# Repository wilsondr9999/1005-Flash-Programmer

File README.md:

# Flash Programmer
Copyright © 2021 by Dan WIlson

This is a simple PCB, firmware, and software that can read and write binary image files to the Microchip SST39 series of flash ROMs.  These flash ROMs are one of the very few flash ROMs on the market that are still active production and in DIP packages, making them a popular replacement for the difficult-to-find AT28 series of EEPROMs.

This programmer handles the SST39SF010, SST39SF020, and SST39SF040 parts (128KB, 256KB, and 512KB respectively).

This programmer’s PCB design uses all through-hole parts for easy soldering.  The general design is based on Ben Eater’s [Arduino-based Flash Programmer](https://www.youtube.com/watch?v=K88pgWhEb1M), using a microcontroller and shift registers to increase the number of available outputs.  Ben’s microcontroller is the Arduino Nano, here I’m using a Microchip PIC16.

The firmware on the PIC16 implements a command protocol that runs over a serial interface.  The board contains a simple RS232 serial level shifter that allows the PC to communicate with the microcontroller.

On the PC, a command line program is provided to read and write to the flash memory.  The command line program is written in Visual C# with Visual Studio.

You can order the PCBs directly from Oshpark with [this](https://oshpark.com/import?url=https://github.com/wilsondr9999/1005-Flash-Programmer/raw/main/1005-Flash-Programmer.zip) link.

Several different licenses apply to this repository and the files within.

All schematics and circuit board designs in the project (all KiCAD files) are licensed under the CERN Open Hardware License Version 2 - Strongly Reciprocal (CERN-OHL-S).

All software and firmware code in the project (all MPLAB and Visual Studio files) are licensed under the GNU Affero General Public License v3.0 (AGPL 3.0).

Bill of Materials, pictures, and documentation (i.e. all other files not covered by the other two licenses above) are licensed under the Creative Commons Attribution Share Alike 4.0 International License (CC-BY-SA-4.0).

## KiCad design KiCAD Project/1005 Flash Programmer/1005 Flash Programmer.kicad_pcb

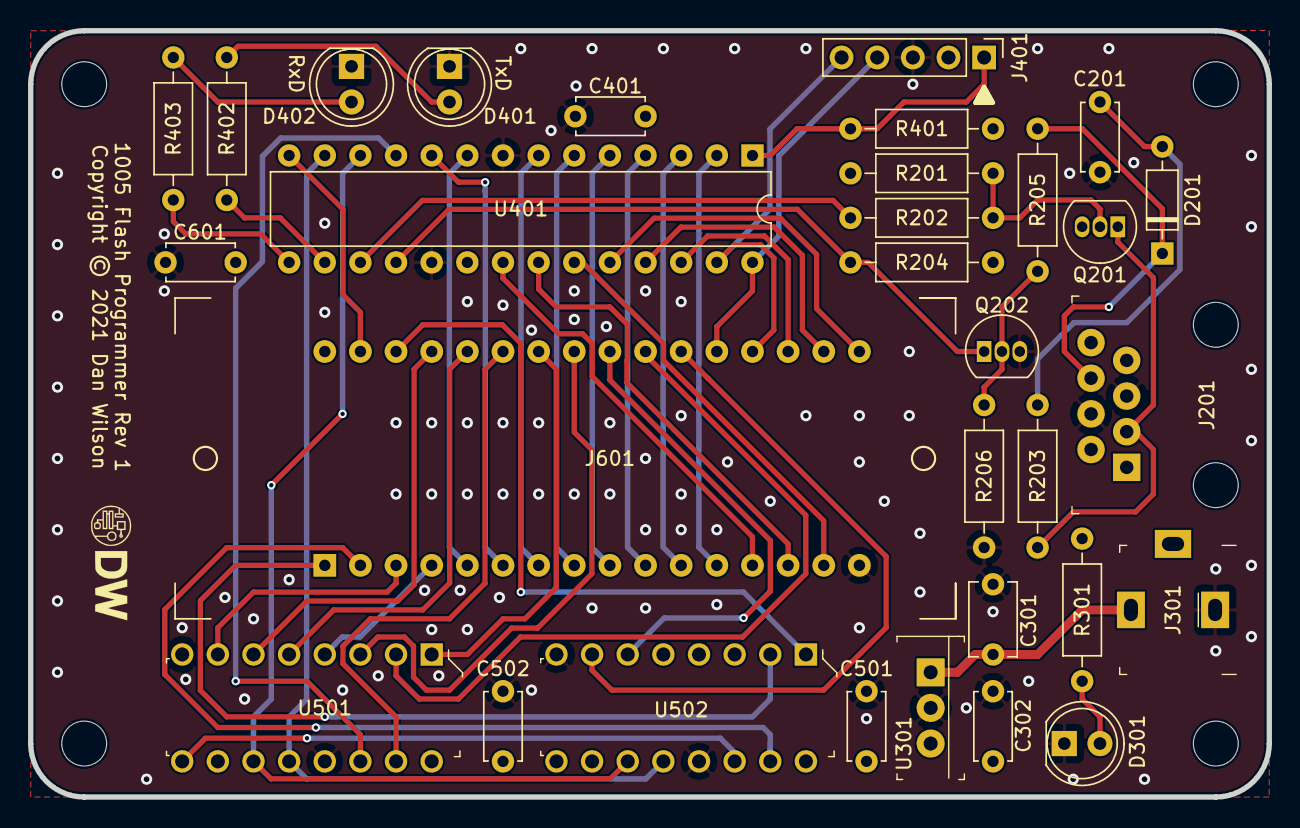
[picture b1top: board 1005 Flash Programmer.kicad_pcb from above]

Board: 4 copper layers, 88.3 x 54.6 mm, 35 parts (0 on the bottom side), 50 nets.

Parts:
C201, C302, C401, C501, C502, C601: 0.1uF; C_Disc_D4.7mm_W2.5mm_P5.00mm
C301: 0.33uF; C_Disc_D5.1mm_W3.2mm_P5.00mm
D201: 1N4148; D_DO-35_SOD27_P7.62mm_Horizontal
D301, D401, D402: LED; LED_D5.0mm
H101, H102, H103, H104: MountingHole; MountingHole_3.2mm_M3
J201: A-2004-2-4-LP-N-R; Ethernet_Jack_54602-908LF
J301: Barrel_Jack_Switch; Barrel_Jack_5.5mmODx2.1mmID_PJ-102A
J401: ICSP; PinHeader_1x05_P2.54mm_Vertical
J601: 32-6554-10
Q201: BC558; TO-92_Inline
Q202: BC548; TO-92_Inline
R201, R202, R204, R401: 10K; R_Axial_DIN0207_L6.3mm_D2.5mm_P10.16mm_Horizontal
R203, R205, R206: 4.7K; R_Axial_DIN0207_L6.3mm_D2.5mm_P10.16mm_Horizontal
R301, R402, R403: 300; R_Axial_DIN0207_L6.3mm_D2.5mm_P10.16mm_Horizontal
U301: L7805CV; TO-220-3
U401: PIC16F15256-xSP; DIP-28_W7.62mm
U501, U502: SN74HC595NE4; DIP-16_W7.62mm

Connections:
/Flash Memory/A0: J601.12, U401.2
/Flash Memory/A1: J601.11, U401.3
/Flash Memory/A2: J601.10, U401.4
/Flash Memory/A3: J601.9, U401.5
/Flash Memory/A4: J601.8, U401.6
/Flash Memory/A5: J601.7, U401.7
/Flash Memory/A6: J601.6, U401.10
/Flash Memory/A7: J601.5, U401.9
/Flash Memory/A8: J601.27, U501.15
/Flash Memory/A9: J601.26, U501.1
/Flash Memory/A10: J601.23, U501.2
/Flash Memory/A11: J601.25, U501.3
/Flash Memory/A12: J601.4, U501.4
/Flash Memory/A13: J601.28, U501.5
/Flash Memory/A14: J601.29, U501.6
/Flash Memory/A15: J601.3, U501.7
/Flash Memory/A16: J601.2, U502.15
/Flash Memory/A17: J601.30, U502.1
/Flash Memory/A18: J601.1, U502.2
/Flash Memory/D0: J601.13, U401.21
/Flash Memory/D1: J601.14, U401.22
/Flash Memory/D2: J601.15, U401.23
/Flash Memory/D3: J601.17, U401.24
/Flash Memory/D4: J601.18, U401.25
/Flash Memory/D5: J601.19, U401.26
/Flash Memory/D6: J401.5, J601.20, U401.27
/Flash Memory/D7: J401.4, J601.21, U401.28
/Flash Memory/~CE: J601.22, U502.7
/Flash Memory/~FL_WE: J601.31, U401.14
/Flash Memory/~OE: J601.24, U502.6
/Micro Controller/LED_uRX: R402.1, U401.16
/Micro Controller/LED_uTX: R403.1, U401.15
/Micro Controller/SR_RCLK: U401.13, U501.12, U502.12
/Micro Controller/SR_SCLK: U401.12, U501.11, U502.11
/Micro Controller/SR_SDATA: U401.11, U501.14
/Micro Controller/USART_uRX: Q202.1, R204.2, U401.18
/Micro Controller/USART_uTX: R202.2, U401.17
/Micro Controller/~MCLR: J401.1, R401.2, U401.1
/UART Level Converter/RxD: J201.3, Q201.1, R203.1
/UART Level Converter/TxD: D201.1, J201.6, R205.1
unnamed: C201.1, D201.2, R203.2
unnamed: C301.1, J301.1, U301.1
unnamed: D301.2, R301.2
unnamed: D401.2, R402.2
unnamed: D402.2, R403.2
unnamed: Q201.2, R201.2, R202.1
unnamed: Q202.2, R205.2, R206.1
unnamed: U501.9, U502.14
VDD: C302.1, C401.1, C501.1, C502.1, C601.1, J401.2, J601.32, Q201.3, R201.1, R204.1, R301.1, R401.1, U301.3, U401.20, U501.10, U501.16, U502.10, U502.16
VSS: C201.2, C301.2, C302.2, C401.2, C501.2, C502.2, C601.2, D301.1, D401.1, D402.1, J201.4, J201.5, J301.2, J401.3, J601.16, Q202.3, R206.2, U301.2, U401.8, U401.19, U501.8, U501.13, U502.8, U502.13

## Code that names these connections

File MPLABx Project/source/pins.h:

/* 
 * File:                pins.h
 * Author:              Dan Wilson
 * Comments:
 * Revision history:    
 */

#ifndef XC_HEADER_PINS_H
#define	XC_HEADER_PINS_H

#include <xc.h> // include processor files - each processor file is guarded.  

// These definitions are to attach convenient names to pins
/*
 * Inputs:  PORTC[7]    UART receive (DTE -> DCE, i.e. computer to PIC)
 * Outputs: PORTC[6]    UART transmit (DCE -> DTE, i.e. PIC to computer)
 *          PORTC[5]    LED for receive
 *          PORTC[4]    LED for transmit
 *          PORTC[0]    Serial data to go out to shift registers
 *          PORTC[1]    Serial clock for shift registers
 *          PORTC[2]    Register clock for shift registers
 *          PORTC[3]    Write Enable for Flash
 *          PORTA       Low-order 8 bits of address
 * Bidir:   PORTB       Data bus to Flash
*/

#define     USART_PICRX     LATCbits.LATC7
#define     USART_PIXTX     LATCbits.LATC6
#define     LED_PICRX       LATCbits.LATC5
#define     LED_PICTX       LATCbits.LATC4
#define     SR_SDATA        LATCbits.LATC0
#define     SR_SCLK         LATCbits.LATC1
#define     SR_RCLK         LATCbits.LATC2
#define     FL_WE           LATCbits.LATC3
#define     FL_ADDRL        PORTA
#define     FL_DATA         PORTB
#define     FL_DATATRIS     TRISB

#endif	/* XC_HEADER_PINS_H */

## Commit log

2023-10-23 v1.0.0.0
    Flash Programmer for SST39 devices.
2023-10-23 1005-README.md.md created from https://stackedit.io/
2023-10-23 1005-README.md created from https://stackedit.io/
2023-10-23 1005-README.md.md updated from https://stackedit.io/
2023-10-23 README.md created from https://stackedit.io/
2023-10-23 README.md updated from https://stackedit.io/
2023-10-23 v1.0.0.1
    Include MBLAB project and Visual Studio project.
2023-10-23 v1.0.0.2
    Include build files from Visual Studio.
2023-10-23 Add .zip file for PCBs
2023-10-24 Create LICENSE-OSHW
2023-10-24 Update LICENSE
2023-10-24 Update LICENSE-OSHW
2023-10-24 Rename LICENSE-OSHW to LICENSE-CERN-OHL-S
2023-10-24 Rename LICENSE to LICENSE-AGPL

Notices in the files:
KiCAD Project/1005 Flash Programmer/1005 Flash Programmer.kicad_pcb:
Copyright © 2021 Dan Wilson
